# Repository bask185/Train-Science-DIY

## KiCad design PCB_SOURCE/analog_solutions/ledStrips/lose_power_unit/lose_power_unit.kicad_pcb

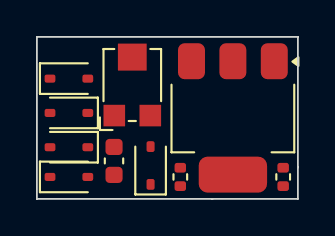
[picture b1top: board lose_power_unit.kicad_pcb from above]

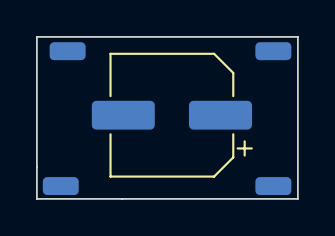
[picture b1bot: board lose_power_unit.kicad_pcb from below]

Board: 2 copper layers, 14.5 x 9.0 mm, 15 parts (5 on the bottom side), 8 nets, no tracks yet.

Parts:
C1: 100nF; C_0603_1608Metric
C2: 100uF; CP_Elec_6.3x7.7
D1, D2, D3, D4, D5: 1N4148WS; D_SOD-323
J1, J2, J3, J4: Conn_01x01_Pin; SolderWirePad_1x01_SMD_1x2mm
R1, R2: 100R; R_0402_1005Metric
RV1: 500R; Potentiometer_Bourns_TC33X_Vertical
U1: LM317_SOT-223; SOT-223-3_TabPin2

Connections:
AC1: D2.1 (K), D4.2 (A), J2.1
AC2: D1.1 (K), D3.2 (A), J1.1
GND: C1.1, C2.2, D1.2 (A), D2.2 (A), J4.1
unnamed: C2.1, D5.2 (A), R1.1
unnamed: J3.1, RV1.1, RV1.2, U1.1 (ADJ)
unnamed: R2.1, RV1.3
unnamed: R2.2, U1.2 (VO)
VCC: C1.2, D3.1 (K), D4.1 (K), D5.1 (K), R1.2, U1.3 (VI)

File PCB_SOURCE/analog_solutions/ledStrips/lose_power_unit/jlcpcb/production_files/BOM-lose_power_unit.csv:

Comment,Designator,Footprint,LCSC
100nF,C1,C_0603_1608Metric,C14663
1N4148WS,"D1,D2,D3,D4,D5",D_SOD-323,C2128
100uF,C2,CP_Elec_6.3x7.7,C59935
500R,RV1,Potentiometer_Bourns_TC33X_Vertical,C720649
LM317_SOT-223,U1,SOT-223-3_TabPin2,C84244
100R,R1,R_0402_1005Metric,
100R,R2,R_0402_1005Metric,

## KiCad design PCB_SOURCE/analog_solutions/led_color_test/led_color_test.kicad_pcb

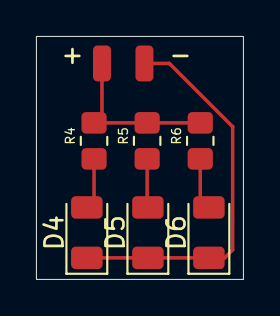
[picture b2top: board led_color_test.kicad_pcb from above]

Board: 2 copper layers, 11.5 x 13.5 mm, 8 parts (0 on the bottom side), 5 nets.

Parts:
+: Conn_01x01; SolderWirePad_1x01_SMD_1x2mm
-: Conn_01x01; SolderWirePad_1x01_SMD_1x2mm
D4, D5, D6: LED; LED_1206_3216Metric
R4, R5, R6: 1k5; R_0805_handsolder-smalltext

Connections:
GND: -.1, D4.1 (K), D5.1 (K), D6.1 (K)
unnamed: D4.2 (A), R4.1
unnamed: D5.2 (A), R5.1
unnamed: D6.2 (A), R6.1
VCC: +.1, R4.2, R5.2, R6.2

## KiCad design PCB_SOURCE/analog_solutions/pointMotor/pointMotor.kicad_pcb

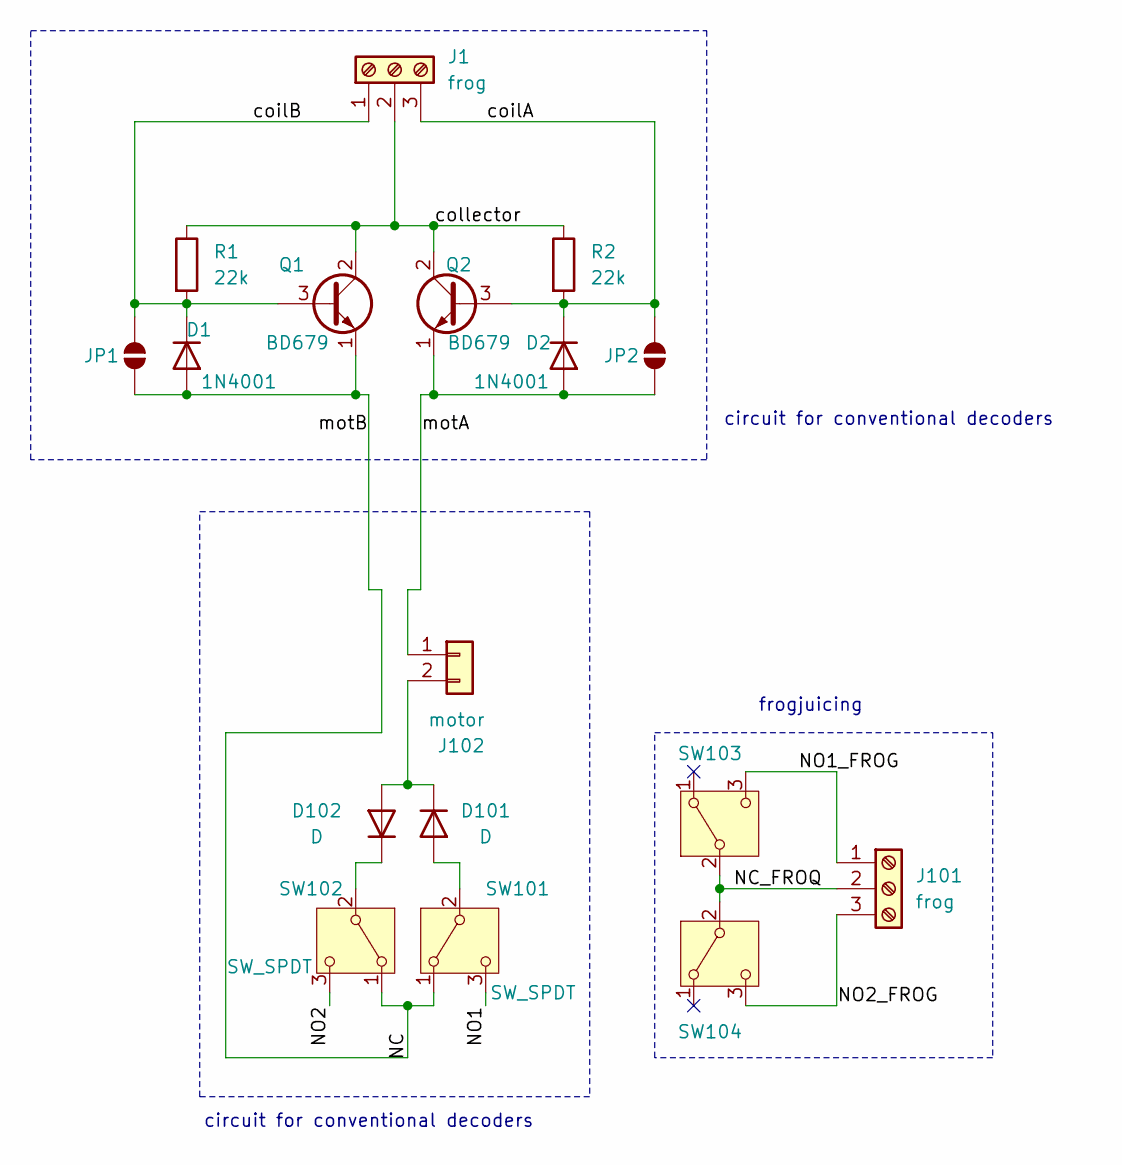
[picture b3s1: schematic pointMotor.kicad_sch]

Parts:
D1, D2: 1N4001; D_DO-34_SOD68_P7.62mm_Horizontal
D101, D102: D; D_DO-34_SOD68_P7.62mm_Horizontal
J1, J101: frog; PhoenixContact_MC_1,5_3-G-3.5_1x03_P3.50mm_Horizontal
J102: motor; N20_motor
JP1, JP2: SolderJumper_2_Open; SolderJumper-2_P1.3mm_Open_RoundedPad1.0x1.5mm
Q1, Q2: BD679; TO-126-3_Vertical
R1, R2: 22k; R_Axial_DIN0204_L3.6mm_D1.6mm_P7.62mm_Horizontal
SW101, SW102, SW103, SW104: SW_SPDT; limitSwitchVertical

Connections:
/NC: D1.2 (A), JP1.1 (A), Q1.1 (E), SW101.1 (A), SW102.1 (A)
/NC_FROQ: J101.2, SW103.2 (B), SW104.2 (B)
/NO1: SW101.3 (C)
/NO1_FROG: J101.1, SW103.3 (C)
/NO2: SW102.3 (C)
/NO2_FROG: J101.3, SW104.3 (C)
/coilA: D2.1 (K), J1.3, JP2.2 (B), Q2.3 (B), R2.2
/coilB: D1.1 (K), J1.1, JP1.2 (B), Q1.3 (B), R1.2
/collector: J1.2, Q1.2 (C), Q2.2 (C), R1.1, R2.1
/motA: D2.2 (A), J102.1, JP2.1 (A), Q2.1 (E)
unnamed: D101.2 (A), SW101.2 (B)
unnamed: D101.1 (K), D102.2 (A), J102.2
unnamed: D102.1 (K), SW102.2 (B)

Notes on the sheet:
frogjuicing
circuit for conventional decoders

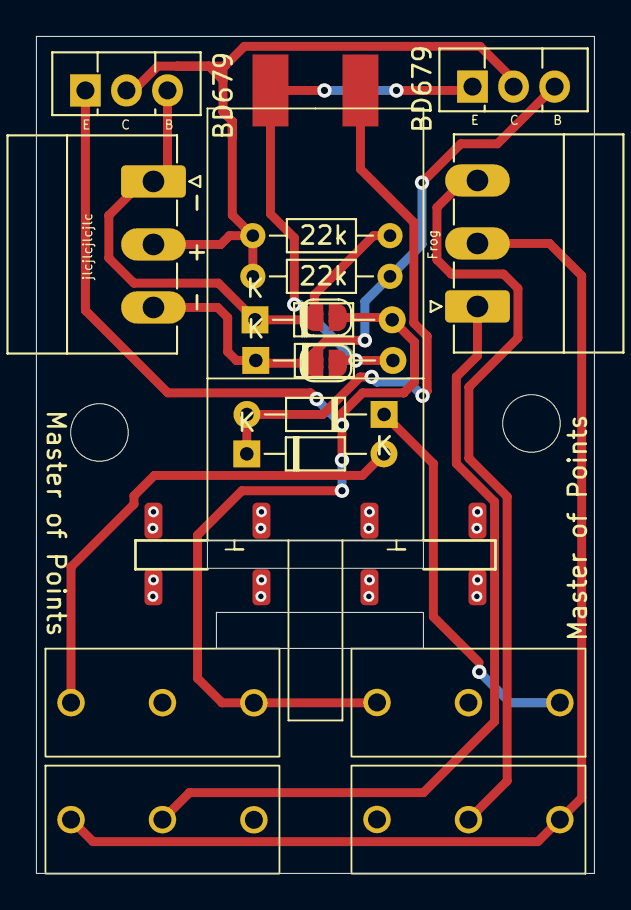
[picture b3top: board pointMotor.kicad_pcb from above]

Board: 2 copper layers, 31.0 x 46.5 mm, 17 parts (0 on the bottom side), 11 nets.

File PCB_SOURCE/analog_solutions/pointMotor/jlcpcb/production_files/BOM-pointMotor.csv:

Comment,Designator,Footprint,LCSC
motor,J102,N20_motor,
frog,J1,"PhoenixContact_MC_1,5_3-G-3.5_1x03_P3.50mm_Horizontal",
frog,J101,"PhoenixContact_MC_1,5_3-G-3.5_1x03_P3.50mm_Horizontal",
D,D102,D_DO-34_SOD68_P7.62mm_Horizontal,
BD679,Q2,TO-126-3_Vertical,
1N4001,D1,D_DO-34_SOD68_P7.62mm_Horizontal,
SW_SPDT,SW103,limitSwitchVertical,
D,D101,D_DO-34_SOD68_P7.62mm_Horizontal,
SW_SPDT,SW102,limitSwitchVertical,
22k,R2,R_Axial_DIN0204_L3.6mm_D1.6mm_P7.62mm_Horizontal,
SW_SPDT,SW104,limitSwitchVertical,
22k,R1,R_Axial_DIN0204_L3.6mm_D1.6mm_P7.62mm_Horizontal,
BD679,Q1,TO-126-3_Vertical,
SW_SPDT,SW101,limitSwitchVertical,
1N4001,D2,D_DO-34_SOD68_P7.62mm_Horizontal,
